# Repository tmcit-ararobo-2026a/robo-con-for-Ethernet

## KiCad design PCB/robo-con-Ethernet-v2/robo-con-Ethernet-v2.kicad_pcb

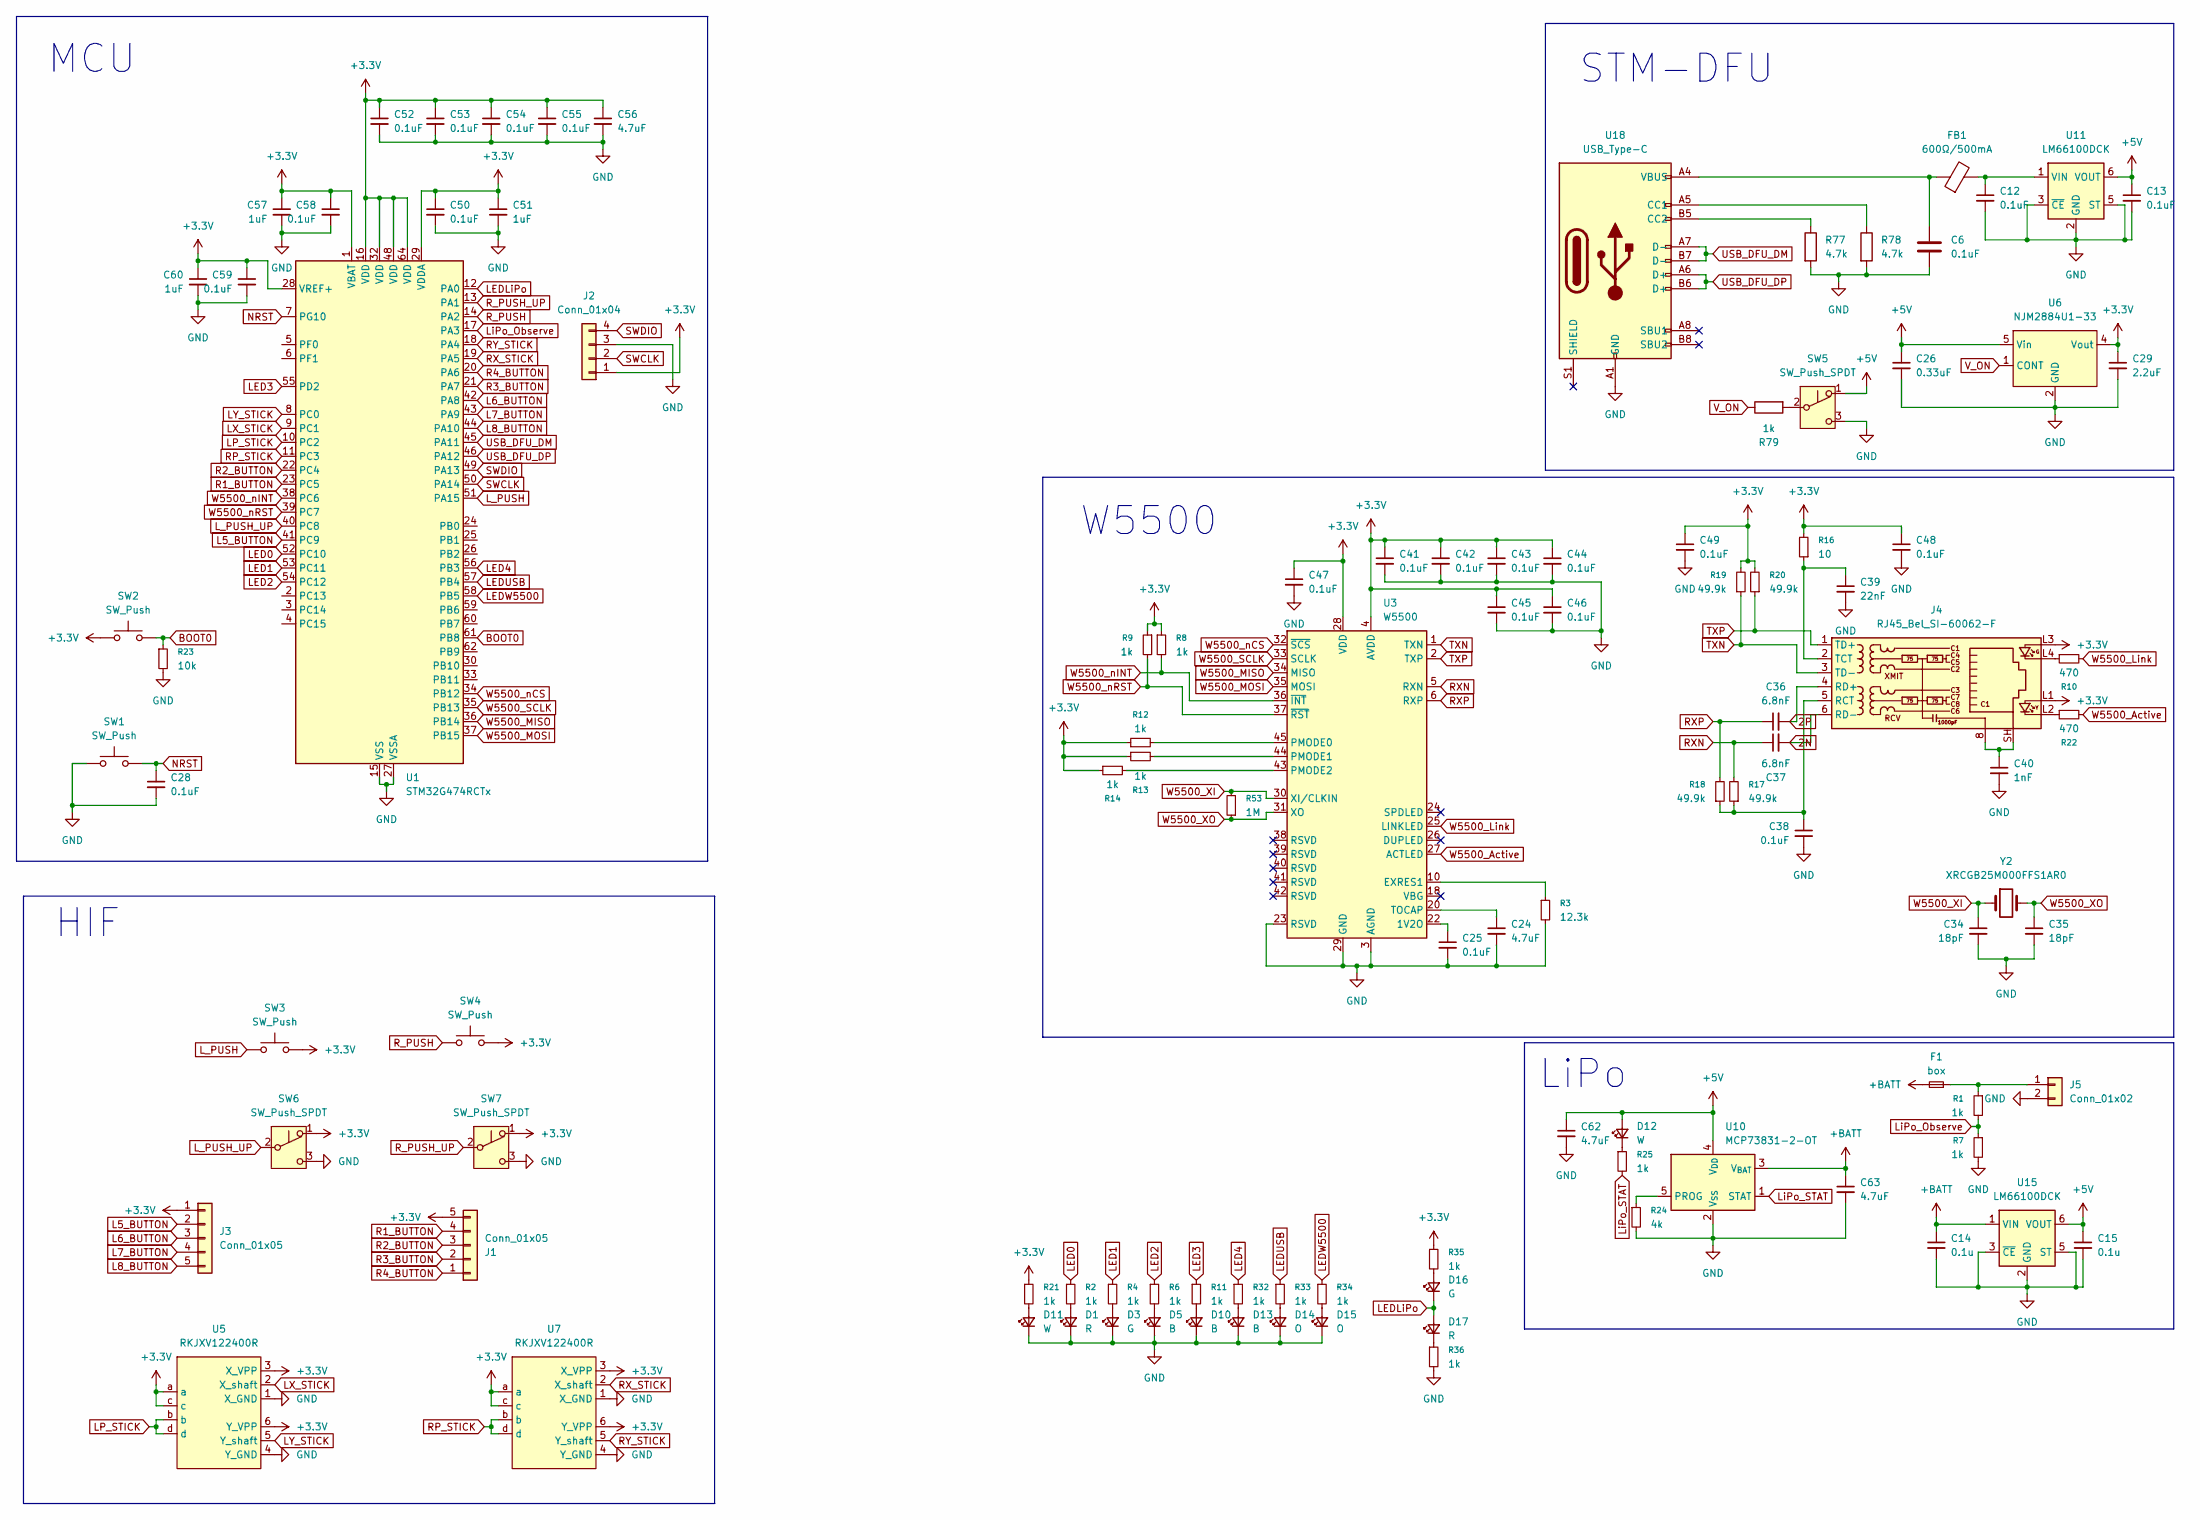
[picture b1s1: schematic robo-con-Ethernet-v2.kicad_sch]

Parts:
C6, C12, C13, C25, C38, C41, C42, C43, C44, C45, C46, C47, C48, C49, C50, C52, C53, C54, C55, C58, C59: 0.1uF; C_0402_1005Metric_Pad0.74x0.62mm_HandSolder
C14, C15: 0.1u; C_0402_1005Metric_Pad0.74x0.62mm_HandSolder
C24, C56, C62, C63: 4.7uF; C_0402_1005Metric_Pad0.74x0.62mm_HandSolder
C26: 0.33uF; C_0402_1005Metric_Pad0.74x0.62mm_HandSolder
C28: 0.1uF; C_0603_1608Metric_Pad1.08x0.95mm_HandSolder
C29: 2.2uF; C_0402_1005Metric_Pad0.74x0.62mm_HandSolder
C34, C35: 18pF; C_0402_1005Metric_Pad0.74x0.62mm_HandSolder
C36, C37: 6.8nF; C_0402_1005Metric_Pad0.74x0.62mm_HandSolder
C39: 22nF; C_0402_1005Metric_Pad0.74x0.62mm_HandSolder
C40: 1nF; C_0603_1608Metric_Pad1.08x0.95mm_HandSolder
C51, C57, C60: 1uF; C_0402_1005Metric_Pad0.74x0.62mm_HandSolder
D1, D17: R; LED_0603_1608Metric_Pad1.05x0.95mm_HandSolder
D3, D16: G; LED_0603_1608Metric_Pad1.05x0.95mm_HandSolder
D5, D10, D13: B; LED_0603_1608Metric_Pad1.05x0.95mm_HandSolder
D11, D12: W; LED_0603_1608Metric_Pad1.05x0.95mm_HandSolder
D14, D15: O; LED_0603_1608Metric_Pad1.05x0.95mm_HandSolder
F1: box; C_0603_1608Metric_Pad1.08x0.95mm_HandSolder
FB1: 600Ω/500mA; L_0603_1608Metric_Pad1.05x0.95mm_HandSolder
J1, J3: Conn_01x05; JST_ZH_B5B-ZR_1x05_P1.50mm_Vertical
J2: Conn_01x04; PinSocket_1x04_P2.54mm_Horizontal
J4: RJ45_Bel_SI-60062-F
J5: Conn_01x02; JST_PH_S2B-PH-K_1x02_P2.00mm_Horizontal
R1, R7: 1k; R_0603_1608Metric_Pad0.98x0.95mm_HandSolder
R2, R4, R6, R8, R9, R11, R12, R13, R14, R21, R25, R32, R33, R34, R35, R36, R79: 1k; R_0402_1005Metric_Pad0.72x0.64mm_HandSolder
R3: 12.3k; R_0402_1005Metric_Pad0.72x0.64mm_HandSolder
R10, R22: 470; R_0603_1608Metric_Pad0.98x0.95mm_HandSolder
R16: 10; R_0402_1005Metric_Pad0.72x0.64mm_HandSolder
R17, R18, R19, R20: 49.9k; R_0402_1005Metric_Pad0.72x0.64mm_HandSolder
R23: 10k; R_0603_1608Metric_Pad0.98x0.95mm_HandSolder
R24: 4k; R_0603_1608Metric_Pad0.98x0.95mm_HandSolder
R53: 1M; R_0402_1005Metric_Pad0.72x0.64mm_HandSolder
R77, R78: 4.7k; R_0402_1005Metric_Pad0.72x0.64mm_HandSolder
SW1, SW2: SW_Push; switch_TVAF06-A020B-R
SW3, SW4: SW_Push; SKHHLPA010
SW5: SW_Push_SPDT; 4MS1R202M6QES
SW6, SW7: SW_Push_SPDT; 8MS8P1B05VS2QES-C13
U1: STM32G474RCTx; LQFP-64_10x10mm_P0.5mm
U3: W5500; LQFP-48_7x7mm_P0.5mm
U5, U7: RKJXV122400R
U6: NJM2884U1-33; SOT-89-5
U10: MCP73831-2-OT; SOT-23-5
U11, U15: LM66100DCK; SOT-363_SC-70-6
U18: USB_Type-C; USB_C_Receptacle_Nelton_5077CR-16-SMC2-BK-TR
Y2: XRCGB25M000FFS1AR0

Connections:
2N: C37.2, J4.6 (RD-)
2P: C36.2, J4.4 (RD+)
+3.3V: C29.1, C41.1, C42.1, C43.1, C44.1, C45.1, C46.1, C47.1, C48.1, C49.1, C50.1, C51.1, C52.1, C53.1, C54.1, C55.1, C56.1, C57.1, C58.1, C59.1, C60.1, J1.5, J2.1, J3.1, J4.L1, J4.L3, R8.1, R9.1, R12.1, R13.1, R14.1, R16.2, R19.2, R20.2, R21.1, R35.1, SW2.1, SW3.2, SW4.2, SW6.1 (A), SW7.1 (A), U1.1 (VBAT), U1.16 (VDD), U1.28 (VREF+), U1.29 (VDDA), U1.32 (VDD), U1.48 (VDD), U1.64 (VDD), U3.4 (AVDD), U3.8 (AVDD), U3.11 (AVDD), U3.15 (AVDD), U3.17 (AVDD), U3.21 (AVDD), U3.28 (VDD), U5.3 (X_VPP), U5.6 (Y_VPP), U5.a, U5.c, U6.4 (Vout), U7.3 (X_VPP), U7.6 (Y_VPP), U7.a, U7.c
+5V: C13.1, C15.1, C26.1, C62.1, D12.2 (A), SW5.1 (A), U6.5 (Vin), U10.4 (V_{DD}), U11.6 (VOUT), U15.6 (VOUT)
+BATT: C14.1, C63.1, F1.2, U10.3 (V_{BAT}), U15.1 (VIN)
BOOT0: R23.1, SW2.2, U1.61 (PB8)
GND: C6.2, C12.2, C13.2, C14.2, C15.2, C24.2, C25.2, C26.2, C28.2, C29.2, C34.2, C35.2, C38.2, C39.2, C40.2, C41.2, C42.2, C43.2, C44.2, C45.2, C46.2, C47.2, C48.2, C49.2, C50.2, C51.2, C52.2, C53.2, C54.2, C55.2, C56.2, C57.2, C58.2, C59.2, C60.2, C62.2, C63.2, D1.1 (K), D3.1 (K), D5.1 (K), D10.1 (K), D11.1 (K), D13.1 (K), D14.1 (K), D15.1 (K), J2.3, J5.2, R3.2, R7.2, R23.2, R24.2, R36.2, R77.2, R78.2, SW1.1, SW5.3 (C), SW6.3 (C), SW7.3 (C), U1.15 (VSS), U1.27 (VSSA), U1.31 (VSS), U1.47 (VSS), U1.63 (VSS), U3.3 (AGND), U3.9 (AGND), U3.14 (AGND), U3.16 (AGND), U3.19 (AGND), U3.23 (RSVD), U3.29 (GND), U3.48 (AGND), U5.1 (X_GND), U5.4 (Y_GND), U6.2 (GND), U7.1 (X_GND), U7.4 (Y_GND), U10.2 (V_{SS}), U11.2 (GND), U11.3 (~CE), U11.5 (ST), U15.2 (GND), U15.3 (~CE), U15.5 (ST), U18.A1 (GND), U18.B1 (GND)
L5_BUTTON: J3.2, U1.41 (PC9)
L6_BUTTON: J3.3, U1.42 (PA8)
L7_BUTTON: J3.4, U1.43 (PA9)
L8_BUTTON: J3.5, U1.44 (PA10)
LED0: R2.1, U1.52 (PC10)
LED1: R4.1, U1.53 (PC11)
LED2: R6.1, U1.54 (PC12)
LED3: R11.1, U1.55 (PD2)
LED4: R32.1, U1.56 (PB3)
LEDLiPo: D16.1 (K), D17.2 (A), U1.12 (PA0)
LEDUSB: R33.1, U1.57 (PB4)
LEDW5500: R34.1, U1.58 (PB5)
LP_STICK: U1.10 (PC2), U5.b, U5.d
LX_STICK: U1.9 (PC1), U5.2 (X_shaft)
LY_STICK: U1.8 (PC0), U5.5 (Y_shaft)
L_PUSH: SW3.1, U1.51 (PA15)
L_PUSH_HOME: SW6.2 (B), U1.40 (PC8)
LiPo_Observe: R1.2, R7.1, U1.17 (PA3)
LiPo_STAT: R25.2, U10.1 (STAT)
NRST: C28.1, SW1.2, U1.7 (PG10)
unnamed: C6.1, FB1.1, U18.A4 (VBUS), U18.B4 (VBUS)
unnamed: C40.1, J4.8, J4.SH
unnamed: D1.2 (A), R2.2
unnamed: D3.2 (A), R4.2
unnamed: D5.2 (A), R6.2
unnamed: D10.2 (A), R11.2
unnamed: D11.2 (A), R21.2
unnamed: D12.1 (K), R25.1
unnamed: D13.2 (A), R32.2
unnamed: D14.2 (A), R33.2
unnamed: D15.2 (A), R34.2
unnamed: D16.2 (A), R35.2
unnamed: D17.1 (K), R36.1
unnamed: J4.L2, R22.1
unnamed: J4.L4, R10.1
unnamed: C38.1, J4.5 (RCT), R17.1, R18.1
unnamed: C39.1, J4.2 (TCT), R16.1
unnamed: F1.1, J5.1, R1.1
unnamed: R79.2, SW5.2 (B)
unnamed: C25.1, U3.22 (1V2O)
unnamed: R3.1, U3.10 (EXRES1)
unnamed: R12.2, U3.45 (PMODE0)
unnamed: R13.2, U3.44 (PMODE1)
unnamed: R14.2, U3.43 (PMODE2)
unnamed: C24.1, U3.20 (TOCAP)
unnamed: R24.1, U10.5 (PROG)
unnamed: C12.1, FB1.2, U11.1 (VIN)
unnamed: R78.1, U18.A5 (CC1)
unnamed: R77.1, U18.B5 (CC2)
R1_BUTTON: J1.4, U1.23 (PC5)
R2_BUTTON: J1.3, U1.22 (PC4)
R3_BUTTON: J1.2, U1.21 (PA7)
R4_BUTTON: J1.1, U1.20 (PA6)
RP_STICK: U1.11 (PC3), U7.b, U7.d
RXN: C37.1, R17.2, U3.5 (RXN)
RXP: C36.1, R18.2, U3.6 (RXP)
RX_STICK: U1.19 (PA5), U7.2 (X_shaft)
RY_STICK: U1.18 (PA4), U7.5 (Y_shaft)
R_PUSH: SW4.1, U1.14 (PA2)
R_PUSH_HOME: SW7.2 (B), U1.13 (PA1)
SWCLK: J2.2, U1.50 (PA14)
SWDIO: J2.4, U1.49 (PA13)
TXN: J4.3 (TD-), R19.1, U3.1 (TXN)
TXP: J4.1 (TD+), R20.1, U3.2 (TXP)
USB_DFU_DM: U1.45 (PA11), U18.A7 (D-), U18.B7 (D-)
USB_DFU_DP: U1.46 (PA12), U18.A6 (D+), U18.B6 (D+)
V_ON: R79.1, U6.1 (CONT)
W5500_Active: R22.2, U3.27 (ACTLED)
W5500_Link: R10.2, U3.25 (LINKLED)
W5500_MISO: U1.36 (PB14), U3.34 (MISO)
W5500_MOSI: U1.37 (PB15), U3.35 (MOSI)
W5500_SCLK: U1.35 (PB13), U3.33 (SCLK)
W5500_XI: C34.1, R53.2, U3.30 (XI/CLKIN), Y2.1
W5500_XO: C35.1, R53.1, U3.31 (XO), Y2.3 (2)
W5500_nCS: U1.34 (PB12), U3.32 (~SCS)
W5500_nINT: R8.2, U1.38 (PC6), U3.36 (~INT)
W5500_nRST: R9.2, U1.39 (PC7), U3.37 (~RST)

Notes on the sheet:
LiPo
W5500
STM-DFU
MCU
HIF

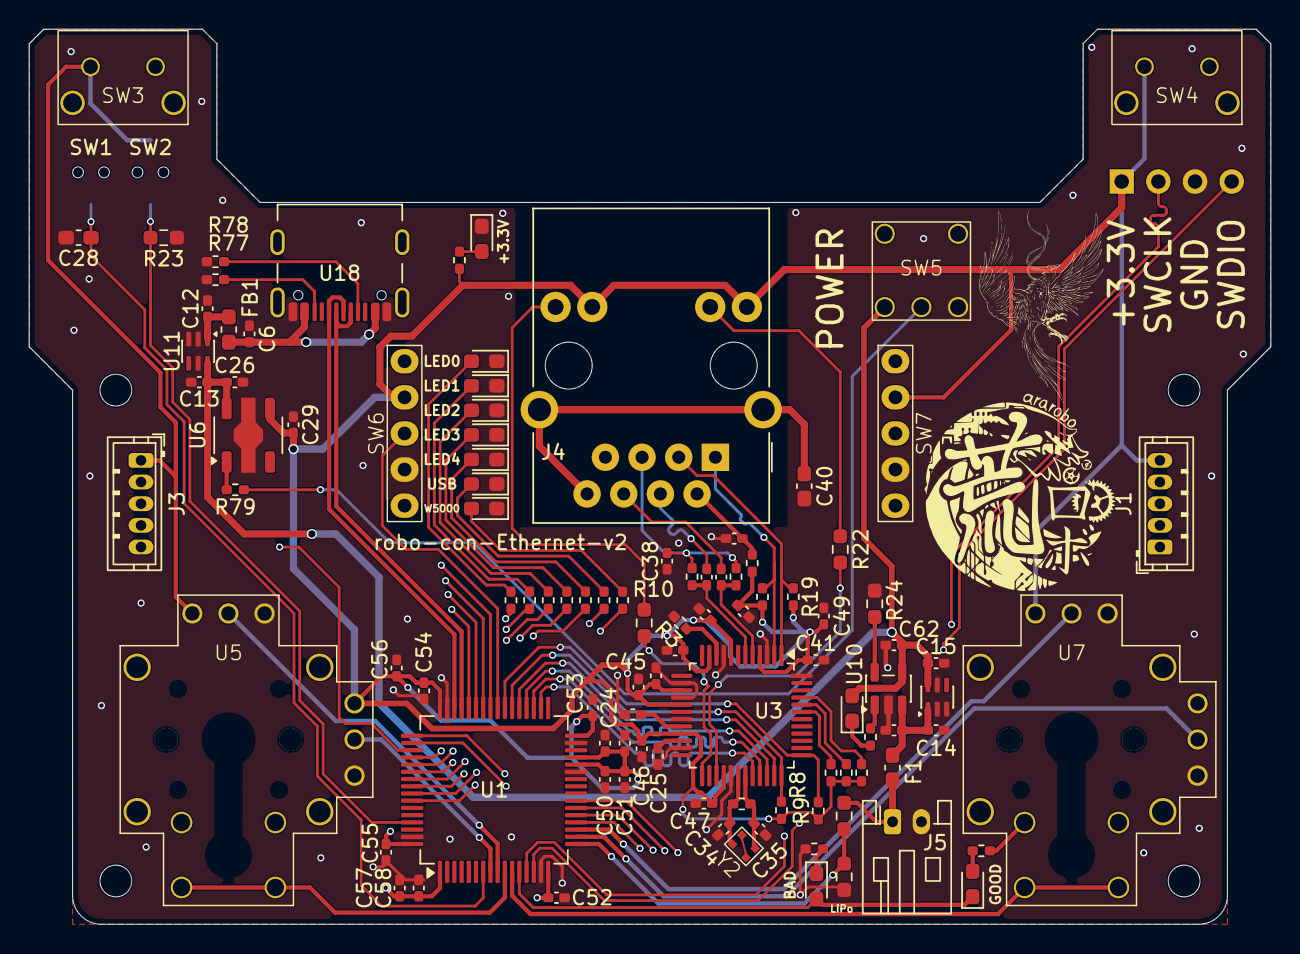
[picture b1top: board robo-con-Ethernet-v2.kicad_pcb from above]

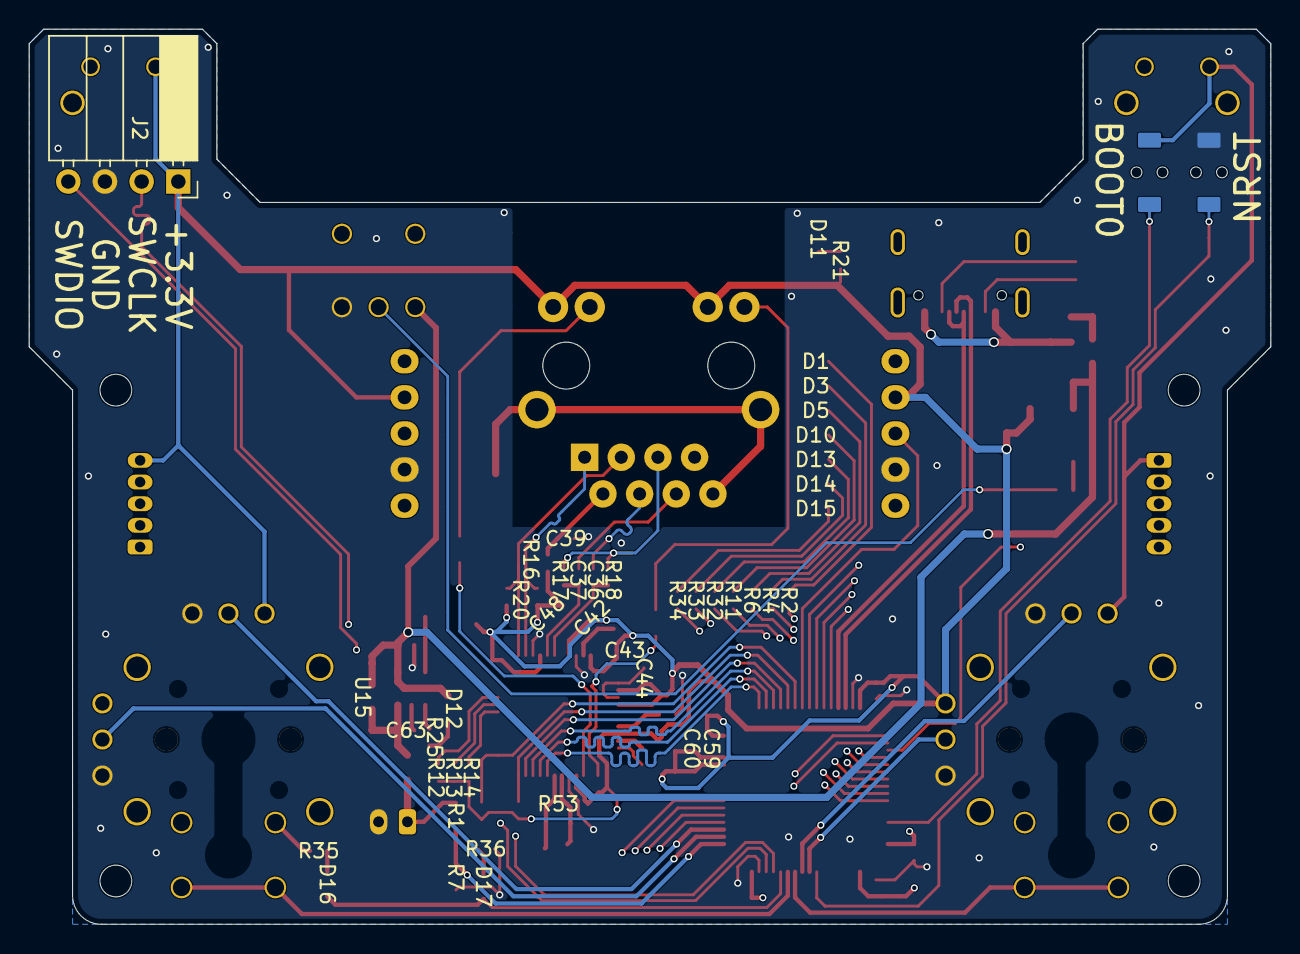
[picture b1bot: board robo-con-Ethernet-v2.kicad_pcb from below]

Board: 4 copper layers, 86.0 x 62.0 mm, 106 parts (3 on the bottom side), 84 nets.

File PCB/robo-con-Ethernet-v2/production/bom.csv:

Designator,Footprint,Quantity,Value,LCSC Part #
"C12, C13, C25, C38, C41, C42, C43, C44, C45, C46, C47, C48, C49, C50, C52, C53, C54, C55, C58, C59, C6",0402,21,0.1uF,
"C14, C15",0402,2,0.1u,
"C24, C56, C62, C63",0402,4,4.7uF,
C26,0402,1,0.33uF,
C28,0603,1,0.1uF,
C29,0402,1,2.2uF,
"C34, C35",0402,2,18pF,
"C36, C37",0402,2,6.8nF,
C39,0402,1,22nF,
C40,0603,1,1nF,
"C51, C57, C60",0402,3,1uF,
"D1, D17",0603,2,R,
"D10, D13, D5",0603,3,B,
"D11, D12",0603,2,W,
"D14, D15",0603,2,O,
"D16, D3",0603,2,G,
F1,0603,1,box,
FB1,0603,1,600Ω/500mA,
"J1, J3",JST_ZH_B5B-ZR_1x05_P1.50mm_Vertical,2,Conn_01x05,
J2,PinSocket_1x04_P2.54mm_Horizontal,1,Conn_01x04,
J4,RJ45_Bel_SI-60062-F,1,RJ45_Bel_SI-60062-F,
J5,JST_PH_S2B-PH-K_1x02_P2.00mm_Horizontal,1,Conn_01x02,
"R1, R7",0603,2,1k,
"R10, R22",0603,2,470,
"R11, R12, R13, R14, R2, R21, R25, R32, R33, R34, R35, R36, R4, R6, R79, R8, R9",0402,17,1k,
R16,0402,1,10,
"R17, R18, R19, R20",0402,4,49.9k,
R23,0603,1,10k,
R24,0603,1,4k,
R3,0402,1,12.3k,
R53,0402,1,1M,
"R77, R78",0402,2,4.7k,
"SW1, SW2",switch_TVAF06-A020B-R,2,SW_Push,
"SW3, SW4",SKHHLPA010,2,SW_Push,
SW5,4MS1R202M6QES,1,SW_Push_SPDT,
"SW6, SW7",8MS8P1B05VS2QES-C13,2,SW_Push_SPDT,
U1,LQFP-64_10x10mm_P0.5mm,1,STM32G474RCTx,
U10,SOT-23-5,1,MCP73831-2-OT,
"U11, U15",SOT-363_SC-70-6,2,LM66100DCK,
U18,USB_C_Receptacle_Nelton_5077CR-16-SMC2-BK-TR,1,USB_Type-C,
U3,LQFP-48_7x7mm_P0.5mm,1,W5500,
"U5, U7",RKJXV122400R,2,RKJXV122400R,
U6,SOT-89-5,1,NJM2884U1-33,
Y2,XRCGB25M000FFS1AR0,1,XRCGB25M000FFS1AR0,

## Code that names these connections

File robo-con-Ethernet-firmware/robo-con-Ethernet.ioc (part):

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Mcu.Name=STM32G474R(B-C-E)Tx
Mcu.Package=LQFP64
Mcu.UserName=STM32G474RETx
PA10.GPIOParameters=GPIO_Label
PA10.GPIO_Label=LED_USB
PA10.Signal=GPIO_Output
PA11.Mode=Device
PA11.Signal=USB_DM
PA12.Mode=Device
PA12.Signal=USB_DP
PA13.Mode=Serial_Wire
PA13.Signal=SYS_JTMS-SWDIO
PA14.Mode=Serial_Wire
PA14.Signal=SYS_JTCK-SWCLK
PA15.GPIOParameters=GPIO_PuPd,GPIO_Label
PA15.GPIO_Label=BUTTON_L1
PA15.GPIO_PuPd=GPIO_PULLDOWN
PA15.Signal=GPIO_Input
PA4.GPIOParameters=GPIO_Speed,PinState,GPIO_Label
PA4.GPIO_Label=SPI1_CS
PA4.GPIO_Speed=GPIO_SPEED_FREQ_HIGH
PA4.PinState=GPIO_PIN_SET
PA4.Signal=GPIO_Output
PA5.Mode=Full_Duplex_Master
PA5.Signal=SPI1_SCK
PA6.Mode=Full_Duplex_Master
PA6.Signal=SPI1_MISO
PA7.Mode=Full_Duplex_Master
PA7.Signal=SPI1_MOSI
PA8.GPIOParameters=GPIO_Label
PA8.GPIO_Label=LEVER_R3
PA8.Signal=GPIO_Input
PA9.GPIOParameters=GPIO_Label
PA9.GPIO_Label=LED_W5500
PA9.Signal=GPIO_Output
PB0.GPIOParameters=GPIO_Label
PB0.GPIO_Label=W5500_IT
PB0.Signal=GPXTI0
PB1.GPIOParameters=PinState,GPIO_Label
PB1.GPIO_Label=W5500_RST
PB1.PinState=GPIO_PIN_SET
PB1.Signal=GPIO_Output
PB11.GPIOParameters=GPIO_Label
PB11.GPIO_Label=STICK_X_R
PB11.Mode=IN14-Single-Ended
PB11.Signal=ADC1_IN14
PB12.GPIOParameters=GPIO_Label
PB12.GPIO_Label=STICK_Y_R
PB12.Mode=IN11-Single-Ended
PB12.Signal=ADC1_IN11
PB13.GPIOParameters=GPIO_PuPd,GPIO_Label
PB13.GPIO_Label=BUTTON_R5
PB13.GPIO_PuPd=GPIO_PULLDOWN
PB13.Signal=GPIO_Input
PB14.GPIOParameters=GPIO_PuPd,GPIO_Label
PB14.GPIO_Label=BUTTON_R6
PB14.GPIO_PuPd=GPIO_PULLDOWN
PB14.Signal=GPIO_Input
PB15.GPIOParameters=GPIO_PuPd,GPIO_Label
PB15.GPIO_Label=BUTTON_R7
PB15.GPIO_PuPd=GPIO_PULLDOWN
PB15.Signal=GPIO_Input
PB3.GPIOParameters=GPIO_Label
PB3.GPIO_Label=LEVER_L3
PB3.Signal=GPIO_Input
PB4.GPIOParameters=GPIO_Label
PB4.GPIO_Label=LEVER_L4
PB4.Signal=GPIO_Input
PB5.GPIOParameters=GPIO_Label
PB5.GPIO_Label=LEVER_L0
PB5.Signal=GPIO_Input
PB6.GPIOParameters=GPIO_Label
PB6.GPIO_Label=LEVER_L2
PB6.Signal=GPIO_Input
PB7.GPIOParameters=GPIO_Label
PB7.GPIO_Label=LEVER_L1
PB7.Signal=GPIO_Input
PC0.GPIOParameters=GPIO_Label
PC0.GPIO_Label=STICK_X_L
PC0.Mode=IN6-Single-Ended
PC0.Signal=ADC1_IN6
PC1.GPIOParameters=GPIO_Label
PC1.GPIO_Label=STICK_Y_L
PC1.Mode=IN7-Single-Ended
PC1.Signal=ADC1_IN7
PC10.GPIOParameters=GPIO_PuPd,GPIO_Label
PC10.GPIO_Label=BUTTON_L2
PC10.GPIO_PuPd=GPIO_PULLDOWN
PC10.Signal=GPIO_Input
PC11.GPIOParameters=GPIO_PuPd,GPIO_Label
PC11.GPIO_Label=BUTTON_L3
PC11.GPIO_PuPd=GPIO_PULLDOWN
PC11.Signal=GPIO_Input
PC12.GPIOParameters=GPIO_PuPd,GPIO_Label
PC12.GPIO_Label=BUTTON_L4
PC12.GPIO_PuPd=GPIO_PULLDOWN
PC12.Signal=GPIO_Input
PC13.GPIOParameters=GPIO_Label
PC13.GPIO_Label=LED4
PC13.Signal=GPIO_Output
PC14-OSC32_IN.GPIOParameters=GPIO_Label
PC14-OSC32_IN.GPIO_Label=LED3
PC14-OSC32_IN.Signal=GPIO_Output
PC15-OSC32_OUT.GPIOParameters=GPIO_Label
PC15-OSC32_OUT.GPIO_Label=LED2
PC15-OSC32_OUT.Signal=GPIO_Output
PC2.GPIOParameters=GPIO_Label
PC2.GPIO_Label=STICK_PUSH_L
PC2.Signal=GPIO_Input
PC3.GPIOParameters=GPIO_Label
PC3.GPIO_Label=STICK_PUSH_R
PC3.Signal=GPIO_Input
PC6.GPIOParameters=GPIO_Label
PC6.GPIO_Label=LEVER_R2
PC6.Signal=GPIO_Input
PC7.GPIOParameters=GPIO_Label
PC7.GPIO_Label=LEVER_R1
PC7.Signal=GPIO_Input
PC8.GPIOParameters=GPIO_Label
PC8.GPIO_Label=LEVER_R0
PC8.Signal=GPIO_Input
PC9.GPIOParameters=GPIO_Label
PC9.GPIO_Label=LEVER_R4
PC9.Signal=GPIO_Input
PF0-OSC_IN.GPIOParameters=GPIO_Label
PF0-OSC_IN.GPIO_Label=LED1
PF0-OSC_IN.Signal=GPIO_Output
PF1-OSC_OUT.GPIOParameters=GPIO_Label
PF1-OSC_OUT.GPIO_Label=LED0
PF1-OSC_OUT.Signal=GPIO_Output
RCC.HSE_VALUE=8000000
RCC.SYSCLKFreq_VALUE=128000000
RCC.SYSCLKSource=RCC_SYSCLKSOURCE_PLLCLK
board=custom
